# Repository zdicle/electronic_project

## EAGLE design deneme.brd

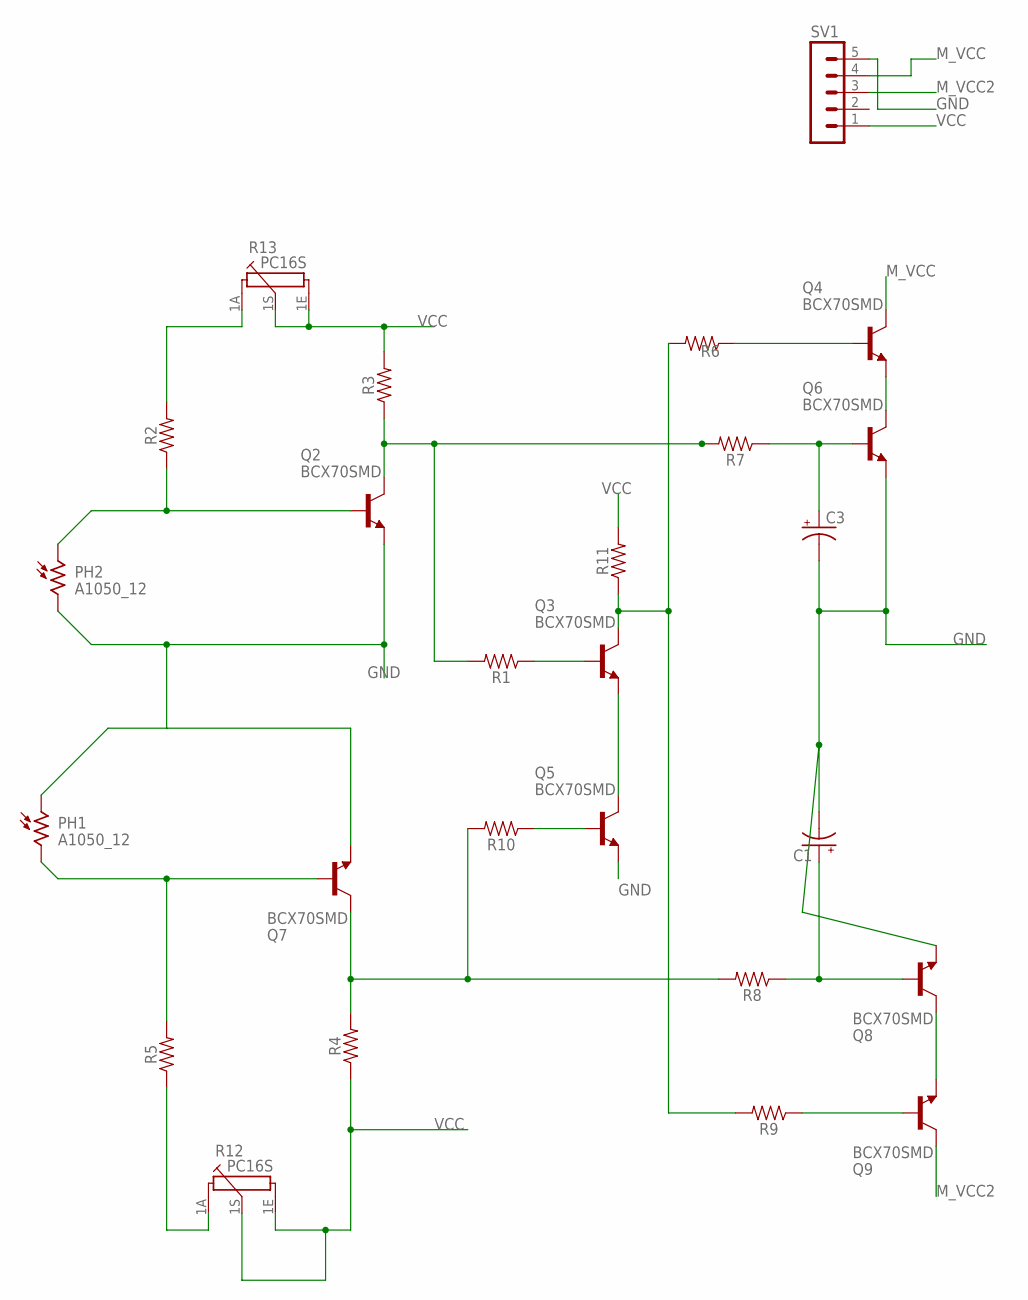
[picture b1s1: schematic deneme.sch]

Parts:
C1, C3: CPOL-USUD-6,3X7,7; UD-6,3X7,7_NICHICON
PH1, PH2: A1050_12; T0-46-A10XX
Q2, Q3, Q4, Q5, Q6, Q7, Q8, Q9: BCX70SMD; SOT23
R1, R2, R3, R4, R5, R6, R7, R8, R9, R10, R11: 0805
R12, R13: PC16S
SV1: MA05-1

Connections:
GND: C1.-, C3.-, PH1.1, PH2.2, Q2.2 (E), Q5.2 (E), Q6.2 (E), Q7.2 (E), Q8.2 (E), SV1.5
M_VCC: Q4.3 (C), SV1.4
M_VCC2: Q9.3 (C), SV1.3
unnamed: R2.2, R13.1A
unnamed: C3.+, Q6.1 (B), R7.1
unnamed: PH2.1, Q2.1 (B), R2.1
unnamed: Q4.1 (B), R6.1
unnamed: PH1.2, Q7.1 (B), R5.2
unnamed: R5.1, R12.1A
unnamed: Q7.3 (C), R4.2, R8.2, R10.2
unnamed: Q5.1 (B), R10.1
unnamed: Q3.2 (E), Q5.3 (C)
unnamed: Q3.1 (B), R1.1
unnamed: Q3.3 (C), R6.2, R9.2, R11.1
unnamed: Q2.3 (C), R1.2, R3.1, R7.2
unnamed: Q4.2 (E), Q6.3 (C)
unnamed: C1.+, Q8.1 (B), R8.1
unnamed: Q8.3 (C), Q9.2 (E)
unnamed: Q9.1 (B), R9.1
VCC: R3.2, R4.1, R11.2, R12.1E, R12.1S, R13.1E, R13.1S, SV1.1

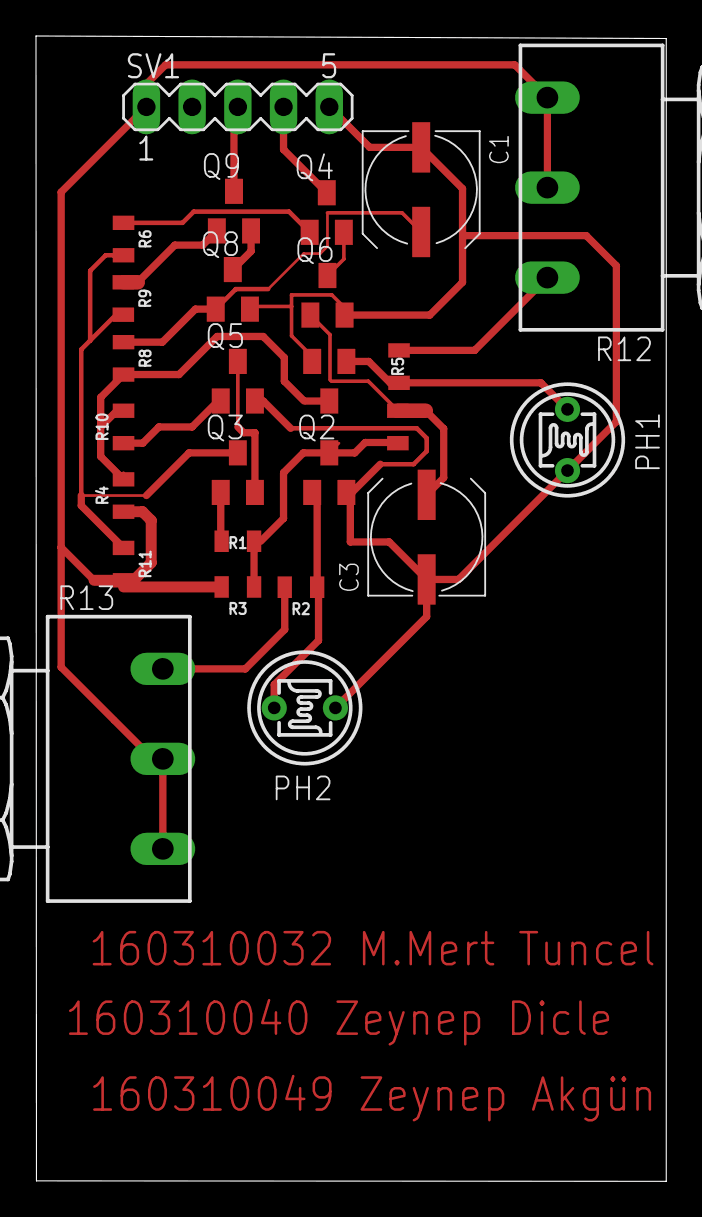
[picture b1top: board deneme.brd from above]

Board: 2 copper layers, 35.0 x 63.6 mm, 26 parts (0 on the bottom side), 20 nets.

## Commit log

2019-05-13 project added
2019-05-16 Ldr changed, curcuit was drawn from the beginning
2019-05-29 project finished
    pot and ldr changed. Shortcomings completed.

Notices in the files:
parts and their libraries:
SparkFun-Resistors: Licensing: Creative Commons ShareAlike 4.0 International - https://creativecommons.org/licenses/by-sa/4.0
